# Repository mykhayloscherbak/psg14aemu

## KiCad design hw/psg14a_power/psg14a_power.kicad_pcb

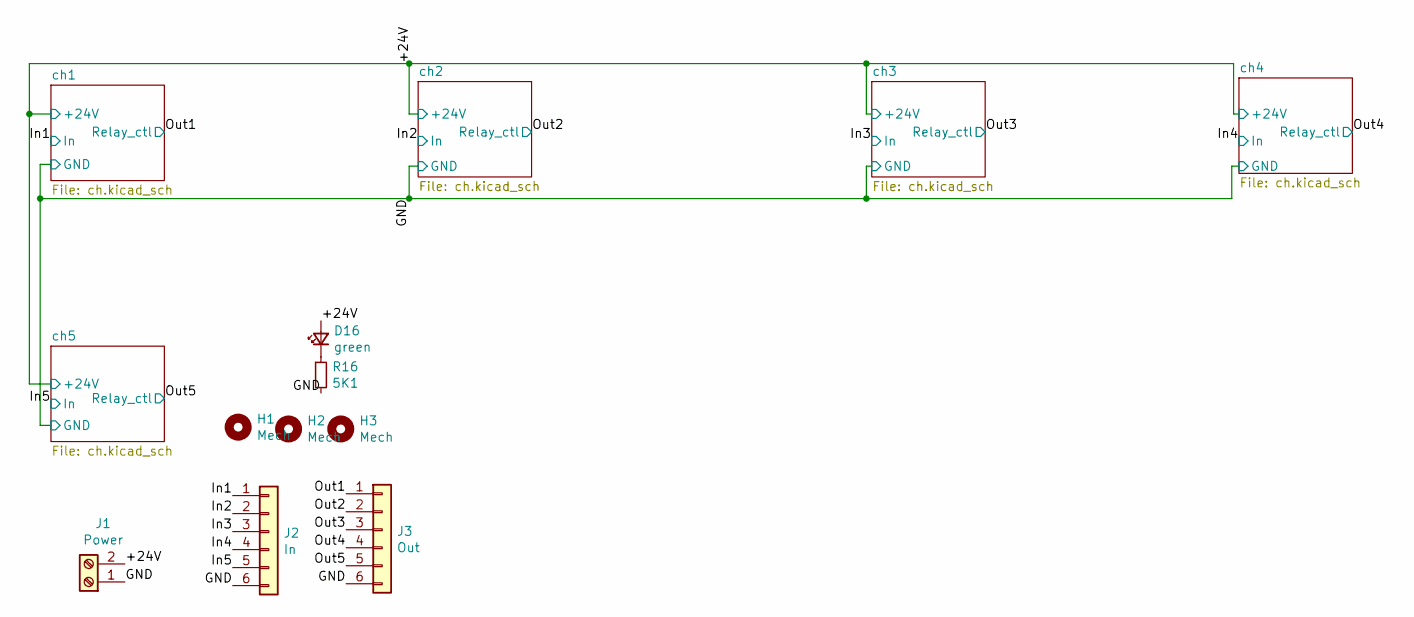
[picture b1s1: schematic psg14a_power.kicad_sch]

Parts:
D16: green; LED_0805_HandSoldering
H1, H2, H3: Mech; MountingHole_3.2mm_M3
J1: Power; TerminalBlock_Phoenix_PT-3.5mm_2pol
J2: In; TerminalBlock_Phoenix_MPT-2.54mm_6pol
J3: Out; TerminalBlock_Phoenix_MPT-2.54mm_6pol
R16: 5K1; R_0805_HandSoldering

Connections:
/+24V: D16.2 (A), J1.2; also elsewhere on the board
/GND: J1.1, J2.6, J3.6, R16.2; also elsewhere on the board
/In1: J2.1; also elsewhere on the board
/In2: J2.2; also elsewhere on the board
/In3: J2.3; also elsewhere on the board
/In4: J2.4; also elsewhere on the board
/In5: J2.5; also elsewhere on the board
/Out1: J3.1; also elsewhere on the board
/Out2: J3.2; also elsewhere on the board
/Out3: J3.3; also elsewhere on the board
/Out4: J3.4; also elsewhere on the board
/Out5: J3.5; also elsewhere on the board
unnamed: D16.1 (K), R16.1

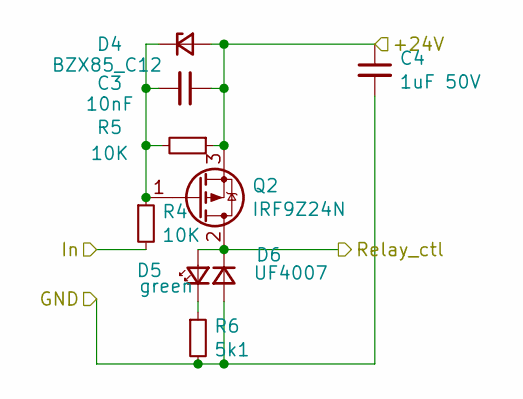
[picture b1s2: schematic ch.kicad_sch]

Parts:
C3: 10nF; C_0805_HandSoldering
C4: 1uF 50V; C_0805_HandSoldering
D4: BZX85_C12; D_DO-41_SOD81_P5.08mm_Vertical_AnodeUp
D5: green; LED_0805_HandSoldering
D6: UF4007; D_DO-41_SOD81_P5.08mm_Vertical_AnodeUp
Q2: IRF9Z24N; TO-220-3_Vertical
R4, R5: 10K; R_0805_HandSoldering
R6: 5k1; R_0805_HandSoldering

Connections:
/+24V: C3.1, C4.1, D4.2 (K), Q2.3 (S), R5.1; also elsewhere on the board
/GND: C4.2, D6.2 (A), R6.2; also elsewhere on the board
/In2: R4.2; also elsewhere on the board
/Out2: D5.2 (A), D6.1 (K), Q2.2 (D); also elsewhere on the board
unnamed: C3.2, D4.1 (A), Q2.1 (G), R4.1, R5.2
unnamed: D5.1 (K), R6.1

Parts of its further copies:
C1, C5, C7, C9: 10nF; C_0805_HandSoldering
C2, C6, C8, C10: 1uF 50V; C_0805_HandSoldering
D1, D7, D10, D13: BZX85_C12; D_DO-41_SOD81_P5.08mm_Vertical_AnodeUp
D2, D8, D11, D14: green; LED_0805_HandSoldering
D3, D9, D12, D15: UF4007; D_DO-41_SOD81_P5.08mm_Vertical_AnodeUp
Q1, Q3, Q4, Q5: IRF9Z24N; TO-220-3_Vertical
R1, R2, R7, R8, R10, R11, R13, R14: 10K; R_0805_HandSoldering
R3, R9, R12, R15: 5k1; R_0805_HandSoldering

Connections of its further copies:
/+24V: C1.1, C2.1, C5.1, C6.1, C7.1, C8.1, C9.1, C10.1, D1.2 (K), D7.2 (K), D10.2 (K), D13.2 (K), Q1.3 (S), Q3.3 (S), Q4.3 (S), Q5.3 (S), R2.1, R8.1, R11.1, R14.1; also elsewhere on the board
/GND: C2.2, C6.2, C8.2, C10.2, D3.2 (A), D9.2 (A), D12.2 (A), D15.2 (A), R3.2, R9.2, R12.2, R15.2; also elsewhere on the board
/In1: R1.2; also elsewhere on the board
/In3: R7.2; also elsewhere on the board
/In4: R10.2; also elsewhere on the board
/In5: R13.2; also elsewhere on the board
/Out1: D2.2 (A), D3.1 (K), Q1.2 (D); also elsewhere on the board
/Out3: D8.2 (A), D9.1 (K), Q3.2 (D); also elsewhere on the board
/Out4: D11.2 (A), D12.1 (K), Q4.2 (D); also elsewhere on the board
/Out5: D14.2 (A), D15.1 (K), Q5.2 (D); also elsewhere on the board
unnamed: C1.2, D1.1 (A), Q1.1 (G), R1.1, R2.2
unnamed: D2.1 (K), R3.1
unnamed: C5.2, D7.1 (A), Q3.1 (G), R7.1, R8.2
unnamed: D8.1 (K), R9.1
unnamed: C7.2, D10.1 (A), Q4.1 (G), R10.1, R11.2
unnamed: D11.1 (K), R12.1
unnamed: C9.2, D13.1 (A), Q5.1 (G), R13.1, R14.2
unnamed: D14.1 (K), R15.1

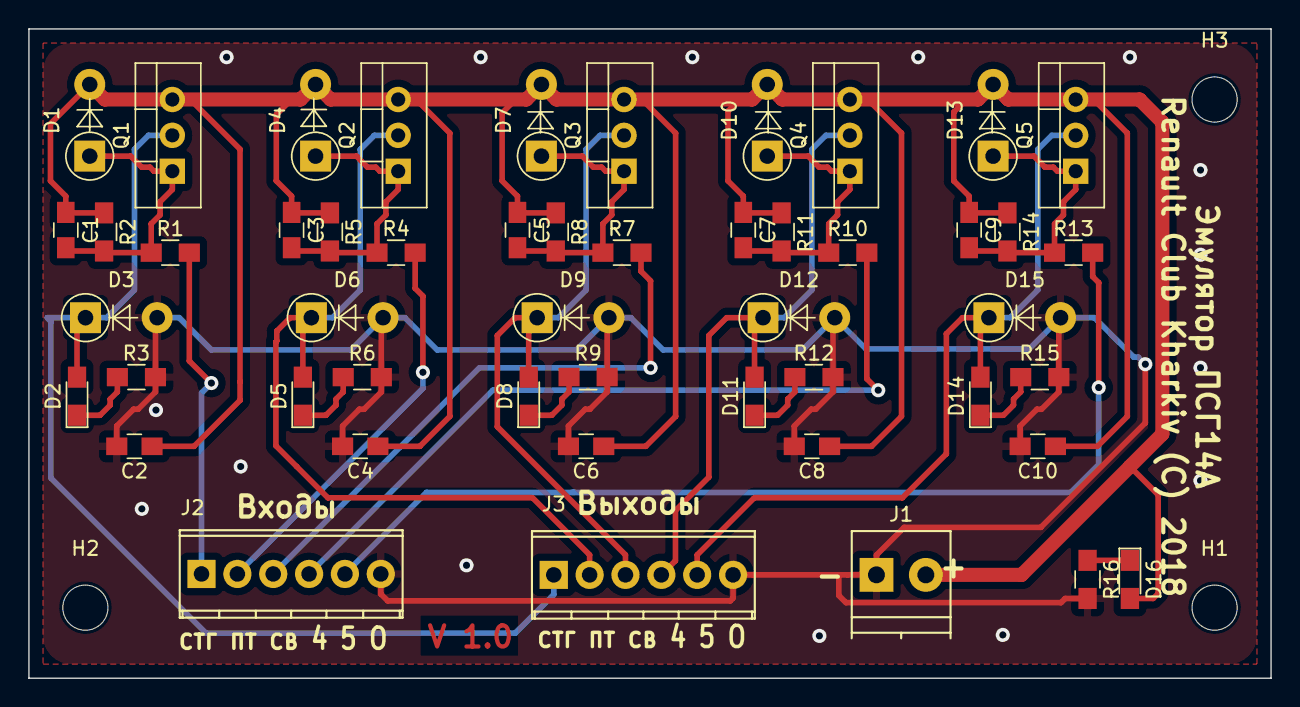
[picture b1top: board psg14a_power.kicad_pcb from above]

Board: 2 copper layers, 88.0 x 46.0 mm, 53 parts (0 on the bottom side), 23 nets.

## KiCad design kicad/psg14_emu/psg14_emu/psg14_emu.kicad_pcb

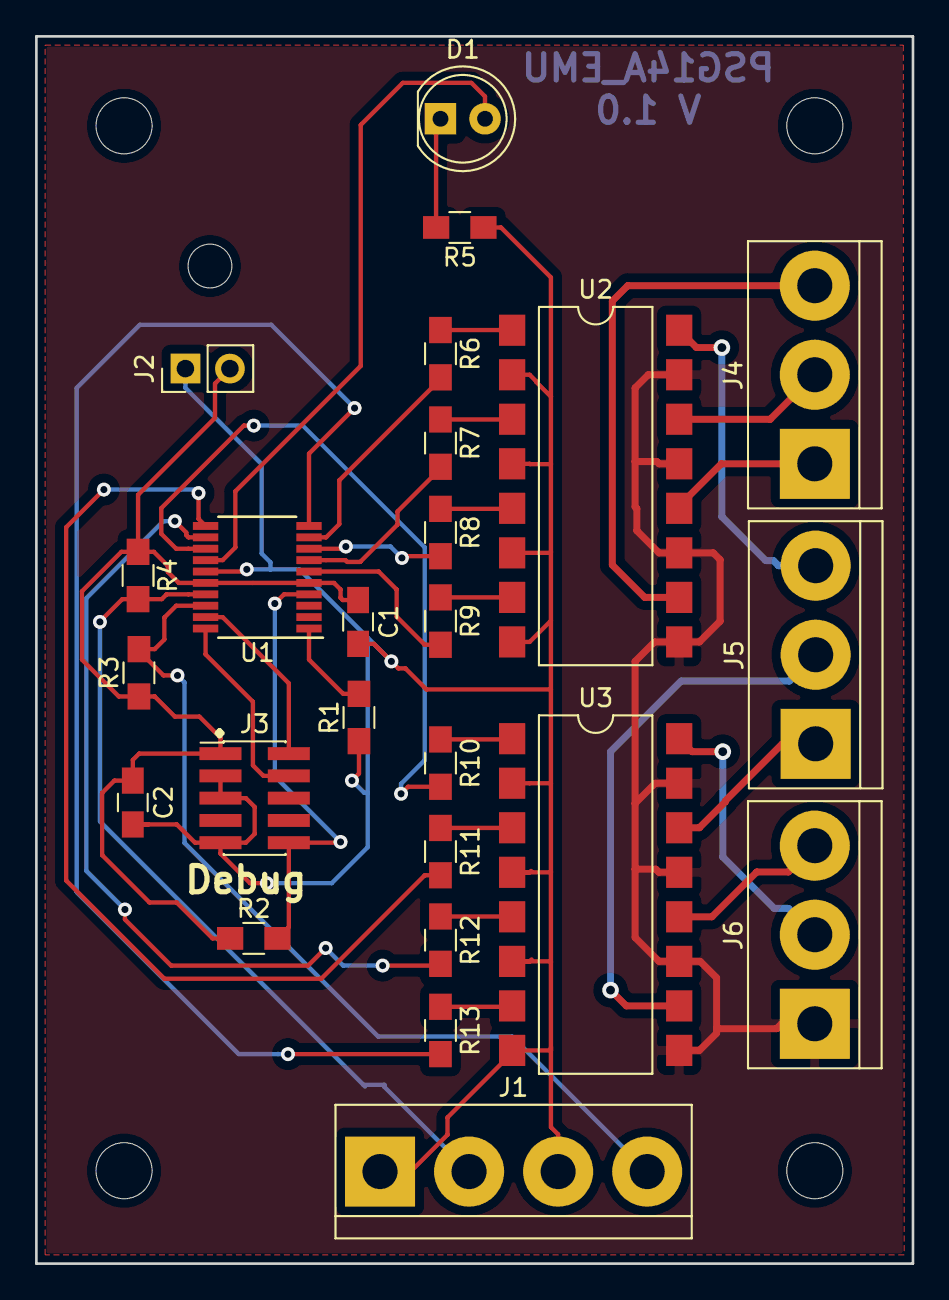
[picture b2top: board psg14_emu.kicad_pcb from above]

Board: 2 copper layers, 50.0 x 70.0 mm, 30 parts (0 on the bottom side), 35 nets.

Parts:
C1, C2: 100nF; C_0805_HandSoldering
D1: LED_GREEN; LED_D5.0mm
J1: Buttons; TerminalBlock_bornier-4_P5.08mm
J2: Battery; Pin_Header_Straight_1x02_Pitch2.54mm
J3: Conn_ARM_JTAG_SWD_10; Pin_Header_Straight_2x05_Pitch1.27mm_SMD
J4, J5, J6: Conn_01x03; TerminalBlock_bornier-3_P5.08mm
MH1: BatteryWire; MountingHole_2.5mm
MH2, MH3, MH4, MH5: MountingHole; MountingHole_3.2mm_M3
R1, R2, R3, R4: 10K; R_0805_HandSoldering
R5: 68; R_0805_HandSoldering
R6, R7, R8, R9, R10, R11, R12, R13: 330; R_0805_HandSoldering
U1: STM32F030F4Px; TSSOP-20_4.4x6.5mm_Pitch0.65mm
U2, U3: LTV-847S; SMDIP-16_W9.53mm_Clearance8mm

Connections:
+BATT: C1.1, C2.1, J2.2, J3.1, R2.1, R3.1, R4.1, U1.5, U1.16
-BATT: C1.2, C2.2, J1.1, J1.3, J2.1, J3.3, J3.5, J3.9, R1.1, R5.1, U1.15, U2.2, U2.4, U2.6, U2.8, U3.2, U3.4, U3.6, U3.8
/B0: J1.2, R4.2, U1.17
/B1: J1.4, R3.2, U1.18
/DO0: R9.2, U1.6
/DO1: R7.2, U1.7
/DO2: R8.2, U1.8
/DO3: R6.2, U1.9
/DO4: R13.2, U1.10
/DO5: R11.2, U1.11
/DO6: R12.2, U1.12
/DO7: R10.2, U1.13
/GND_O: J6.1, U2.9, U2.11, U2.13, U2.15, U3.9, U3.11, U3.13, U3.15
/NRST: J3.10, R2.2, U1.4
/OUT0: J4.3, U2.10
/OUT1: J4.2, U2.14
/OUT2: J4.1, U2.12
/OUT3: J5.3, U2.16
/OUT4: J5.2, U3.10
/OUT5: J5.1, U3.14
/OUT6: J6.3, U3.12
/OUT7: J6.2, U3.16
/SWDCLK: J3.4, U1.20
/SWDIO: J3.2, U1.19
unnamed: D1.1, R5.2
unnamed: D1.2, U1.14
unnamed: R1.2, U1.1
unnamed: R6.1, U2.1
unnamed: R7.1, U2.3
unnamed: R8.1, U2.5
unnamed: R9.1, U2.7
unnamed: R10.1, U3.1
unnamed: R11.1, U3.3
unnamed: R12.1, U3.5
unnamed: R13.1, U3.7

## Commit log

2018-10-13 [psg14_emu] project stared
2018-10-13 [psg14_emu]
2018-10-14 [psg14_emu] Schematics ready
2018-10-16 [psg14_emu] Assignements
2018-10-17 [psg14_emu] PCB tracing
2018-10-17 [psg14_emu] Ready for production
2018-10-17 [psg14_emu] Sent to production
2018-10-17 [psg14_emu]Moved to upper dir
2018-10-20 [psg14_emu] BOM added
2018-11-09 [psg14_emu] Bom changed
2018-12-01 [psg14a_power]First commit
2018-12-10 [psg14a_power]Schematics finished
2018-12-12 [psg14a-power]Components placed
2018-12-13 [psg14a] looking how to copy blocks
2018-12-14 [psg14a_power]New route added
2018-12-16 [psg14a_power] Switch to multiple sheets layout
2018-12-18 [psg14a_power] Ready for replication which does not work ;-)
2018-12-18 [psg14a_power]New components placement
2018-12-19 [psg14a_power] New layout
2018-12-20 Share project "zone" into "https://miklscherbak.svn.cloudforge.com/avr/pc"
2018-12-20 [psg14a_power] New layout again
2018-12-21 [psg14a_power] Routing in progress
2018-12-22 [psg14a_power]Ready for review by Ioan the Greatest
2018-12-22 [Psg14a_power] Ioan the Greatest was drunk. Ready for production
2018-12-26 [psg14a_emu]First commit
2018-12-28 [psg14a_emu] Linker script added
2018-12-30 [psg14a_emu]First buildable commit
2018-12-30 [psg14a_emu]First runnable commit
2018-12-31 [psg14a_emu]Clock init added. Nothing works now
2018-12-31 [psg14a_emu]temp commit
2019-01-01 [psg14a_emu]Timers init added. GPIO started
2019-01-01 [psg14a_emu]Timers init added. GPIO started2
2019-01-02 [psg14a_emu]Gpio works for LED
2019-01-02 [psg14a_emu]Led blink works now
2019-01-02 [psg14a_emu]Cosmetics
2019-01-04 [psg14a_emu]Doxygen added
2019-01-04 [psg14a_emu]Temp
2019-01-06 [psg14a_emu]Tables added but do not work
2019-01-07 [psg14a_emu]Tables work now. Real gpio must be checked
2019-01-09 [psg14a_emu]Modes switching works now. Sleep TBD
2019-01-11 [psg14a_emu]Sleep added. Does not wake up sometimes
2019-01-26 [psg14a]project changed
2019-02-09 [psg14a_power] bom added
2019-02-09 [psg14a_emu]Totally broken
2019-03-23 [psg14a_emu]works for test purposes
2019-04-27 [psg14a_emu]Added 500ms pause after button is pressed before start mode. Sleep mode still does not work
2019-05-11 [psg14a_emu]Still can not go to sleep mode
2019-05-25 [psg14a_emu]First iteration ended. Cyclogramms added
2019-06-08 Share project "neo7" into "https://miklscherbak.svn.cloudforge.com/avr"
2019-06-08 [psg14a_emu]Priming fuel timing changed to 5000/800 ms
2019-06-28 [psg14_a]Fixed unstable startup
2019-07-27 [psg14a_emu]Destroyed everyting
2020-01-11 [psg14a_emu]?
2020-01-25 [psg14_emu]Channel for 36v added
2020-02-06 [start128]Gerbers and schematics added for start128
2020-02-19 [psg14_emu]Timings changed
2024-08-04 Renaming dirs
2024-08-04 Project files deleted
2024-08-04 Added doc target
2024-08-05 Doxygen in progress
2024-08-08 All_with_docs target added
2024-08-08 UML diagrams added
2024-08-10 Cosmetics
2024-08-12 Adding COG
2024-08-13 Cog in progress
2024-08-28 Cog is working. TODO: scaling
2024-09-10 Scaling options added
2024-09-16 Develop/adding doxygen (#1)
    * Doxygen fixed
    * Plantuml added
2024-09-16 .pdf added. Converted to Kicad7
2024-09-17 Unneeded files deleted
2024-09-18 Diode rotated
2024-09-21 Develop/hw (#2)
    * Converted to Kicad 7.x
    * Zener diode wrong footprint fixed
2024-09-21 Python code split to separate file. File is doxygenized now.
2024-09-21 Cosmetic changes
2024-09-22 Develop/extracting python (#3)
    * Python code split to separate file. File is doxygenized now.
2024-09-22 Site added
2025-08-06 Cyclogram timimgs changed

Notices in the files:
hw/psg14a_power/psg14a_power.kicad_pcb:
Renault Club Kharkiv (C) 2018
